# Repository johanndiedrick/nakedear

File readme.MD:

# Naked Ear
## Introduction to Tools and Techniques for Sound Art

### Description

This workshop is for artists and researchers wanting to become more
familiar with the potential of sound. Our focus will be on expanding our
understanding of sound in an environment. This requires a basic vocabulary
for talking about sound as a material, as well as the ability to make and
use tools for investigating and manipulating sound for creative purposes.

Our frame of reference will be Good Vibrations, a mobile listening kit that
allows "acoustic explorers" to find the lesser audible soun=
ds in their
environment. By using hand- made microphones and amplifiers, listeners can
tune into the subtle vibrations

that usually go unnoticed. The project encourages listeners to reimagine
their sonic environment by playfully exploring the world through their ears.

The workshop will introduce participants to the world of sound art, while
providing techniques for making tools for creating these experiences. This
will include

the fabrication of hand-made microphones, speakers, and amplifiers for use
in installations, performances, and scientific research. The goal of the
workshop is

to take these tools into the field and use them for artistic investigation
and public engagement.

### Content

For the first session, students will be introduced to the sound art
practice. Examples of seminal and canonical works will be presented, giving
students a taste of potential projects. From there we will move onto
describing the basic physics and properties of sound. Our introduction will
end with an explanation of how sound is received through a microphone,
amplified with an amplifier, and sent through a speaker to produce audible
sound.

The rest of the workshop will consist of building a contact microphone, a
speaker and an amplifier. From there we will take our tools out into nearby
McCarren Park and amplify found sounds.

### Outline

**Session 1**

-  Hour 1: Introductions

- Overview of sound art

- Overview of physics of sound

- Overview of how micrphone, speaker, and amplifier work

-  Hour 2: Microphone

- Contact microphone build

- https://www.youtube.com/watch?v=P8iAshJ1Pk0

- https://www.youtube.com/watch?v=yz5CM0eCGA0

-  Hour 3: Speaker

- Speaker build

-  Hour 4: Amplifier

- Amplifier build on breadboard

**Session 2**

- Hour 1:

- Amplifier build on PCB

- Hour 2:

- Placing amplifier in enclosure

- Hour 3:

- Exploring McCarren Park with listening kits

- Hour 4:

- Presentation of experiments

## Student Profile

Students do not need to have any electronic experience. Some soldering
experience is a plus but is not required. An expertise knowledge of sound
and how it works is also not required. A large part of the workshop is to
teach that to you! A strong curiosity and willingness to learn about sound
is the only basic requirement.

## What students get from your profile; software, materials to work

- One contact mic

- One speaker

- One amplifier

- One custom enclosure with custom pcb

- Reference material (excerpts from Electronic Music Handbook, David Dunn's
microphone PDF etc.)

## Pre requisites and preparation for the workshop

Things we will need in the studio for each student:

- Soldering station

- Solder

- Multimeter

- Wire

- Jumper wires

## Instructor short bio

Johann Diedrick makes installations, performances, and software that allow
people to activly participate in the production of sound. His work has been
exhibited internationally in numerous group exhibitions, conferences and
festivals, including the New Interfaces for Musical Expression (NIME)
conference in Daejeon and Seoul, Korea, the Invisible Places, Sounding
Cities conference in Viseu, Portugal, and the Dumbo Arts Festival in
Brooklyn, New York. He received his Masters in Professional Studies at the
Interactive Telecommunications Program (ITP) at Tisch School of the Arts at
New York University, focusing on sound art. During time at ITP he was a
researcher at the InterLab at the Yamaguchi Center for Arts and Media
(YCAM) in Yamaguchi, Japan. Afterwards he worked as an interactive software
developer at Qosmo in Tokyo, Japan. He is currently a software developer at
the Metropolitan Museum of Art.

## Instructor Links, website, social media

Website: http://www.johanndiedrick.com

Github: @jdiedrick

Twitter: @jdiedrick

Instagram: @johanndiedrick

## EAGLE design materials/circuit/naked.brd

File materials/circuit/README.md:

Based on this circuit:

http://www.basicanalogcircuits.com/Session_8.html

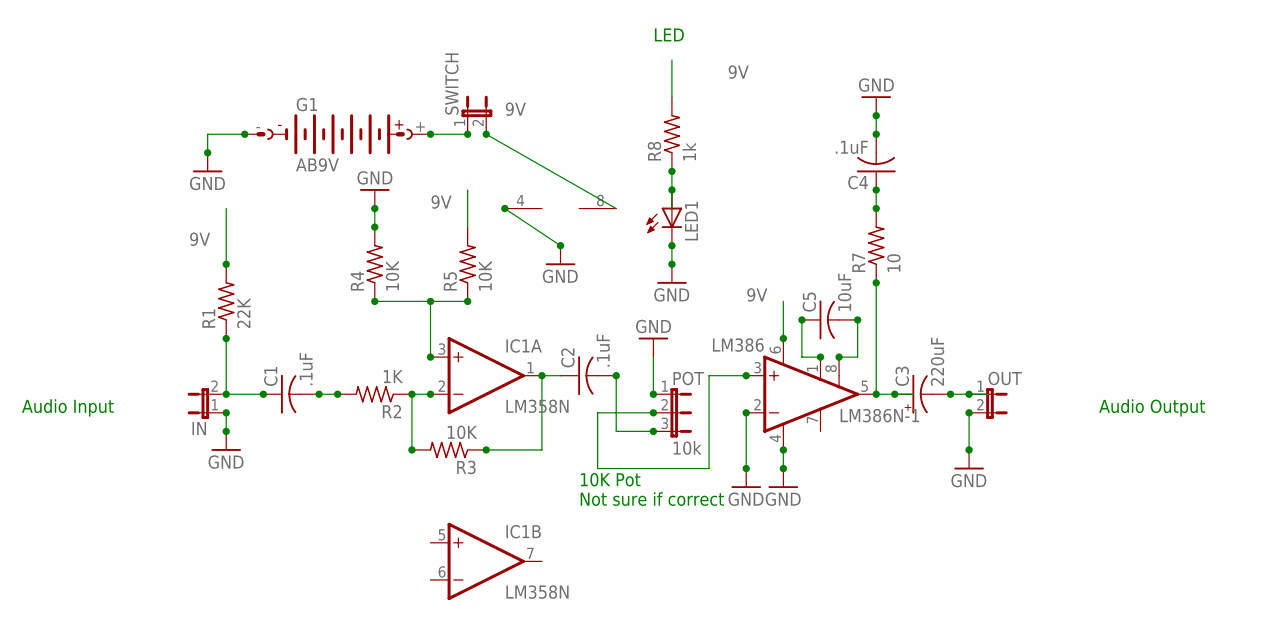
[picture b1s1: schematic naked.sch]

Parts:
C1, C2, C4: .1uF; C025-024X044
C3: 220uF; E3,5-8
C5: 10uF; C025-024X044
G1: AB9V
IC1: LM358N; DIL08
IN: JP1E; JP1
LED1: LED5MM
LM386: LM386N-1; DIL08
OUT: JP1E; JP1
POT: 10k; JP2
R1: 22K; 0204/7
R2: 1K; 0204/7
R3, R4, R5: 10K; 0204/7
R7: 10; 0204/7
R8: 1k; 0204/7
SWITCH: JP1E; JP1

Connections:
9V: IC1.8 (V+), LM386.6 (VS), R1.2, R5.2, R8.2, SWITCH.2
GND: C4.2, G1.-, IC1.4 (V-), IN.1, LED1.K (C), LM386.2 (-IN), LM386.4 (GND), OUT.2, POT.1, R4.2
unnamed: G1.+, SWITCH.1
unnamed: C1.1, IN.2, R1.1
unnamed: C1.2, R2.2
unnamed: IC1.2 (-IN), R2.1, R3.2
unnamed: C5.1, LM386.1 (GAIN)
unnamed: IC1.3 (+IN), R4.1, R5.1
unnamed: C2.1, IC1.1 (OUT), R3.1
unnamed: C2.2, POT.3
unnamed: LM386.3 (+IN), POT.2
unnamed: C3.+, LM386.5 (OUT), R7.1
unnamed: C3.-, OUT.1
unnamed: LED1.A, R8.1
unnamed: C4.1, R7.2
unnamed: C5.2, LM386.8 (GAIN)

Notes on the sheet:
Audio Input
Audio Output
LED
10K Pot Not sure if correct

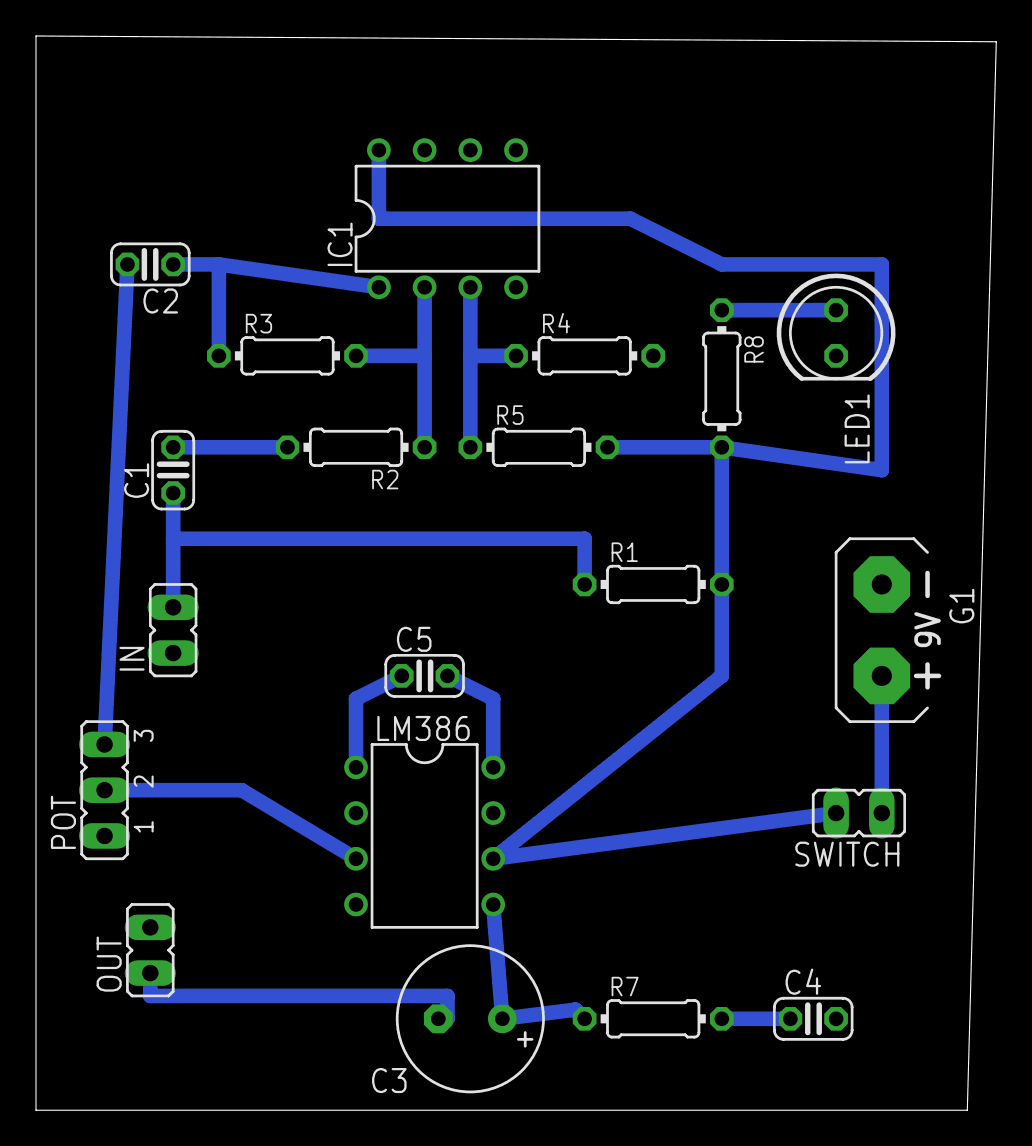
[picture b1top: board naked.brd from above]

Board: 2 copper layers, 53.4 x 59.7 mm, 20 parts (0 on the bottom side), 16 nets.

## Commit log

2015-06-23 updated references
2015-09-14 updated syllabus
2015-09-16 added circuit and breadboard design
2015-09-17 deleted brd, updated board w led and pot
2015-09-17 added readme for circuit
2015-09-25 updates to materials and syllabus
2015-09-25 updated materials
2015-10-08 added box designs, circuit, presentation etc
2015-10-09 updated presentation
2015-10-12 added post mortems
2015-10-12 added presentation
2015-10-13 renamed pres dir
2015-10-21 added info on mics, and hem pdf
2015-10-21 edited presentation
2015-12-23 updates with othermill and references
2016-01-04 added some resources
2016-01-04 updating references
2016-01-04 added more references
2016-01-24 added updated circut designs, updated some online references
2016-01-28 updated online resources
